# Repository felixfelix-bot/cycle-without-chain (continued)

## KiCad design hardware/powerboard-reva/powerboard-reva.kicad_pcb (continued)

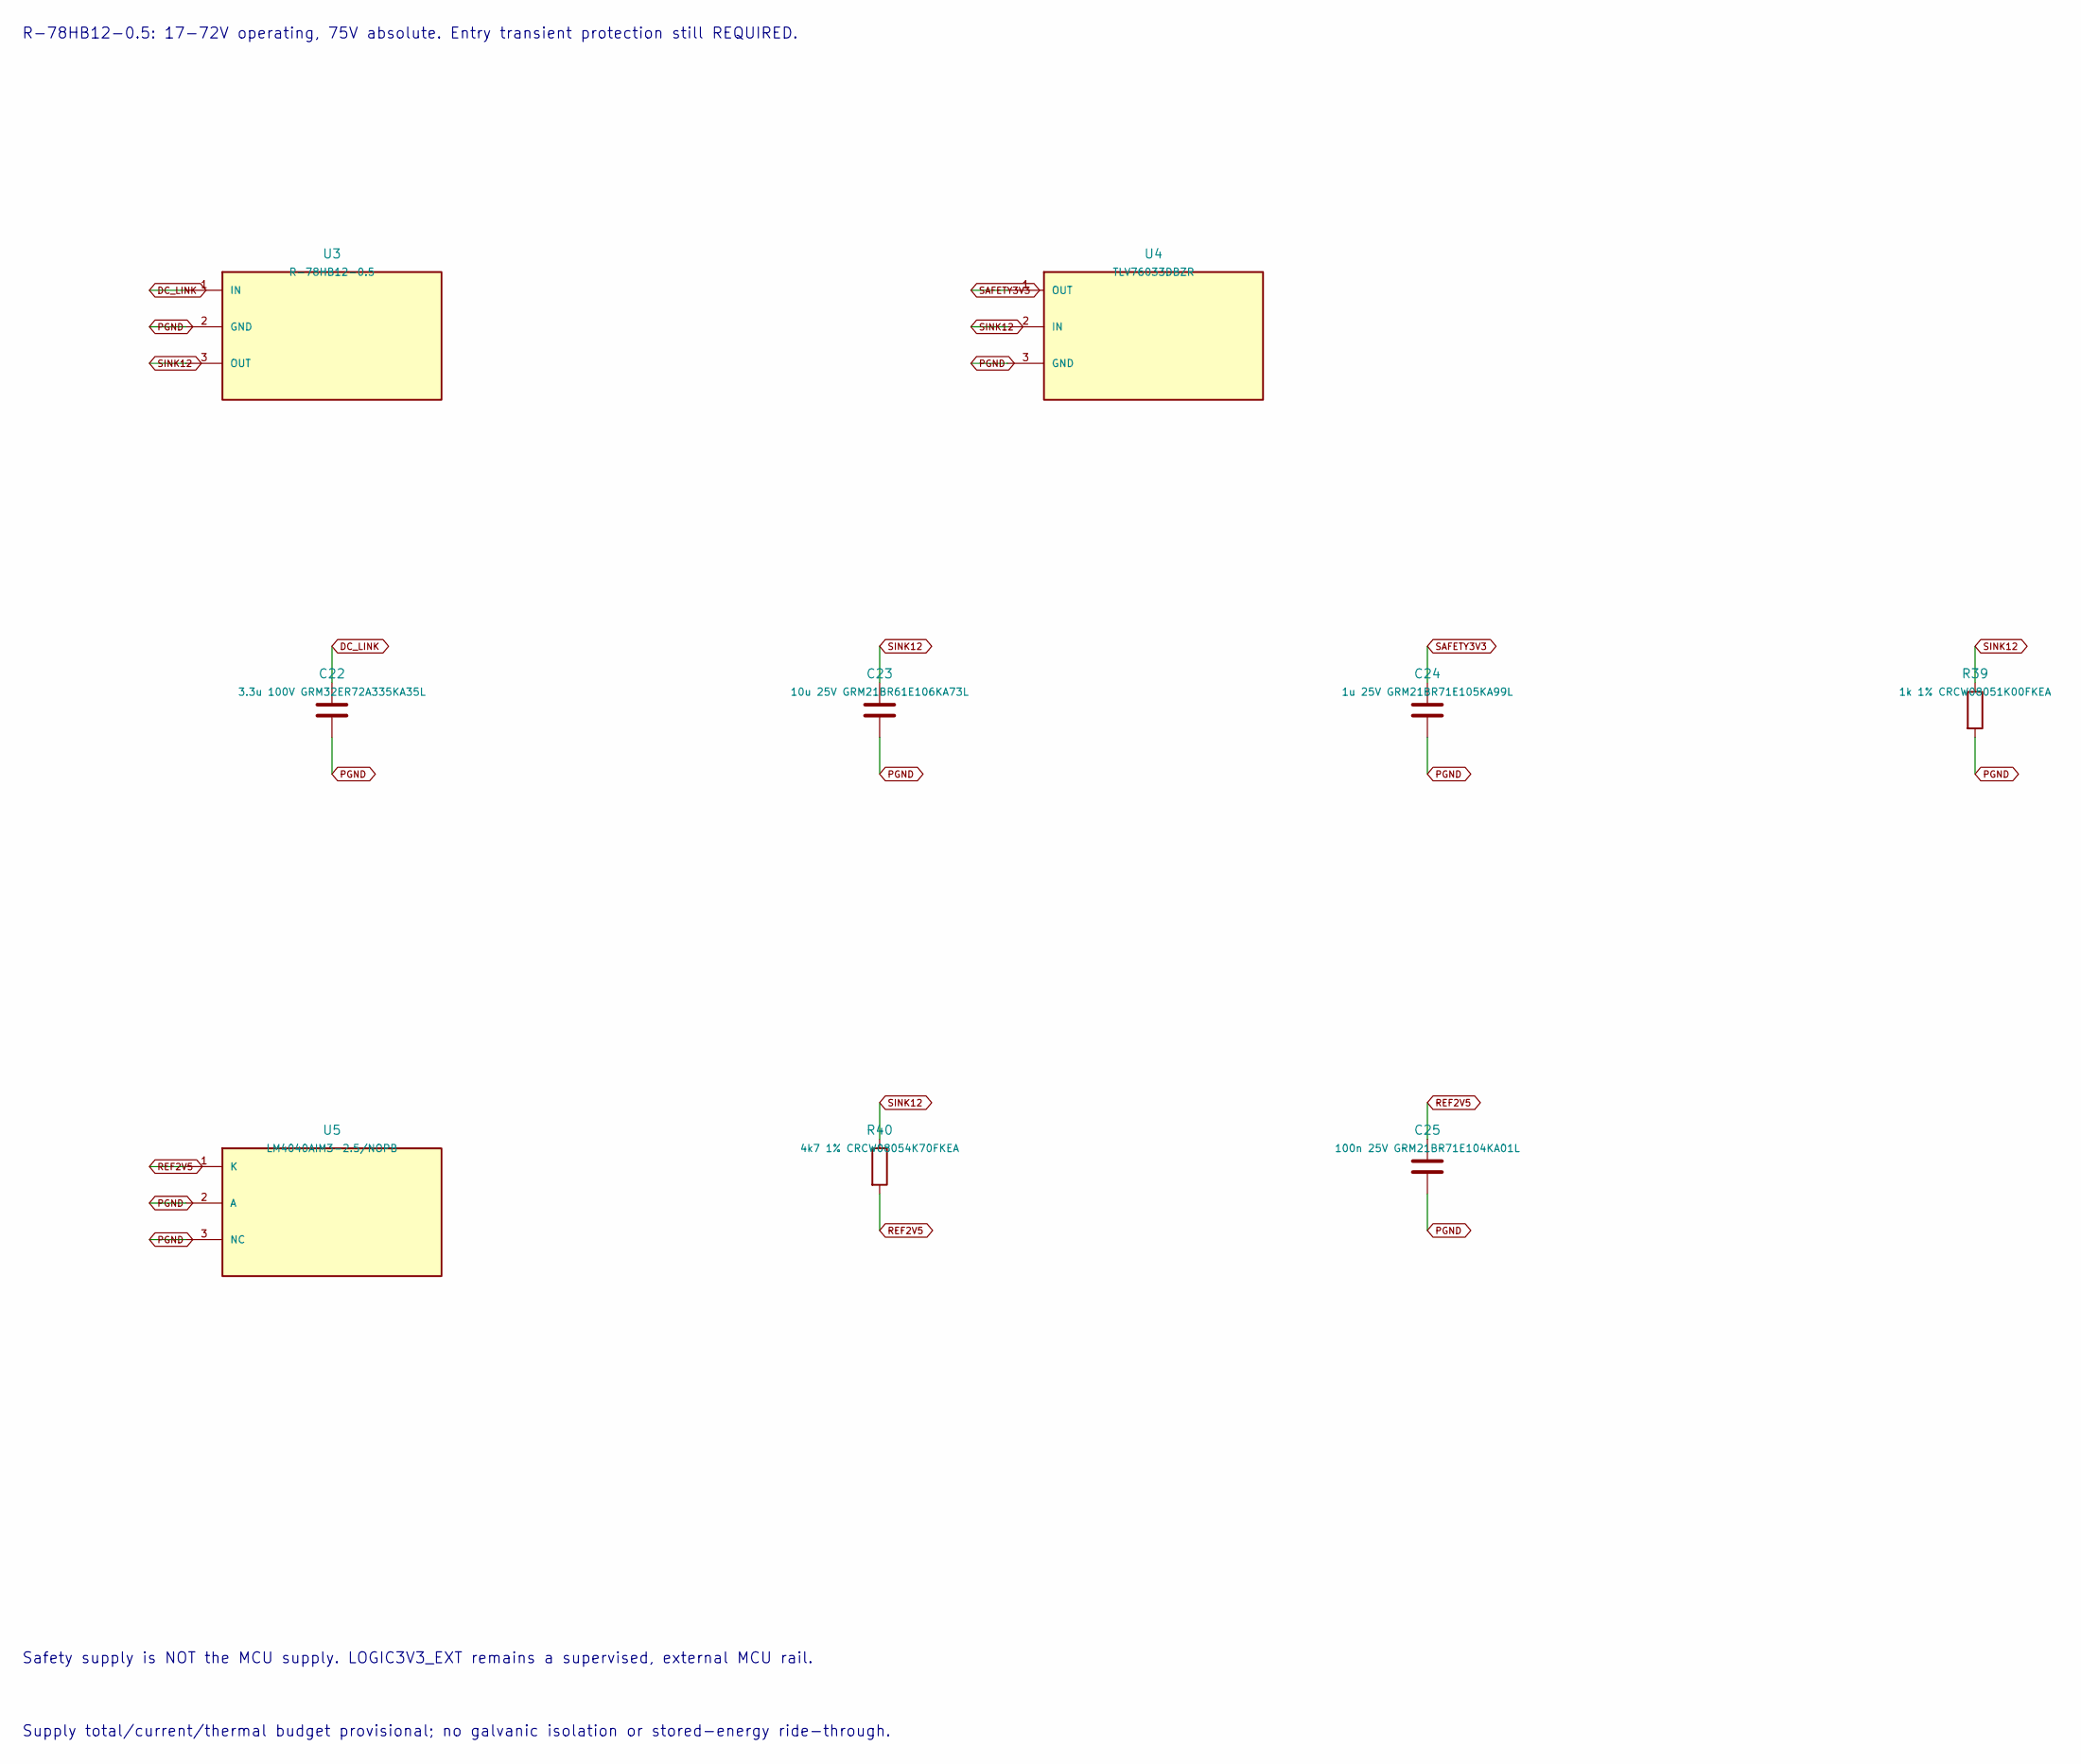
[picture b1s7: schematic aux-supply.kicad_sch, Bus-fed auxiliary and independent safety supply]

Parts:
C22: 3.3u 100V GRM32ER72A335KA35L; C_1210_3225Metric
C23: 10u 25V GRM21BR61E106KA73L; C_0805_2012Metric
C24: 1u 25V GRM21BR71E105KA99L; C_0805_2012Metric
C25: 100n 25V GRM21BR71E104KA01L; C_0805_2012Metric
R39: 1k 1% CRCW08051K00FKEA; R_0805_2012Metric
R40: 4k7 1% CRCW08054K70FKEA; R_0805_2012Metric
U3: R-78HB12-0.5; Converter_DCDC_RECOM_R-78HB-0.5_THT
U4: TLV76033DBZR; SOT-23
U5: LM4040AIM3-2.5/NOPB; SOT-23

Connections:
DC_LINK: C22.1, U3.1 (IN); also elsewhere on the board
PGND: C22.2, C23.2, C24.2, C25.2, R39.2, U3.2 (GND), U4.3 (GND), U5.2 (A), U5.3 (NC); also elsewhere on the board
REF2V5: C25.1, R40.2, U5.1 (K); also elsewhere on the board
SAFETY3V3: C24.1, U4.1 (OUT); also elsewhere on the board
SINK12: C23.1, R39.1, R40.1, U3.3 (OUT), U4.2 (IN); also elsewhere on the board

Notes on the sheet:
R-78HB12-0.5: 17-72V operating, 75V absolute. Entry transient protection still REQUIRED.
Safety supply is NOT the MCU supply. LOGIC3V3_EXT remains a supervised, external MCU rail.
Supply total/current/thermal budget provisional; no galvanic isolation or stored-energy ride-through.

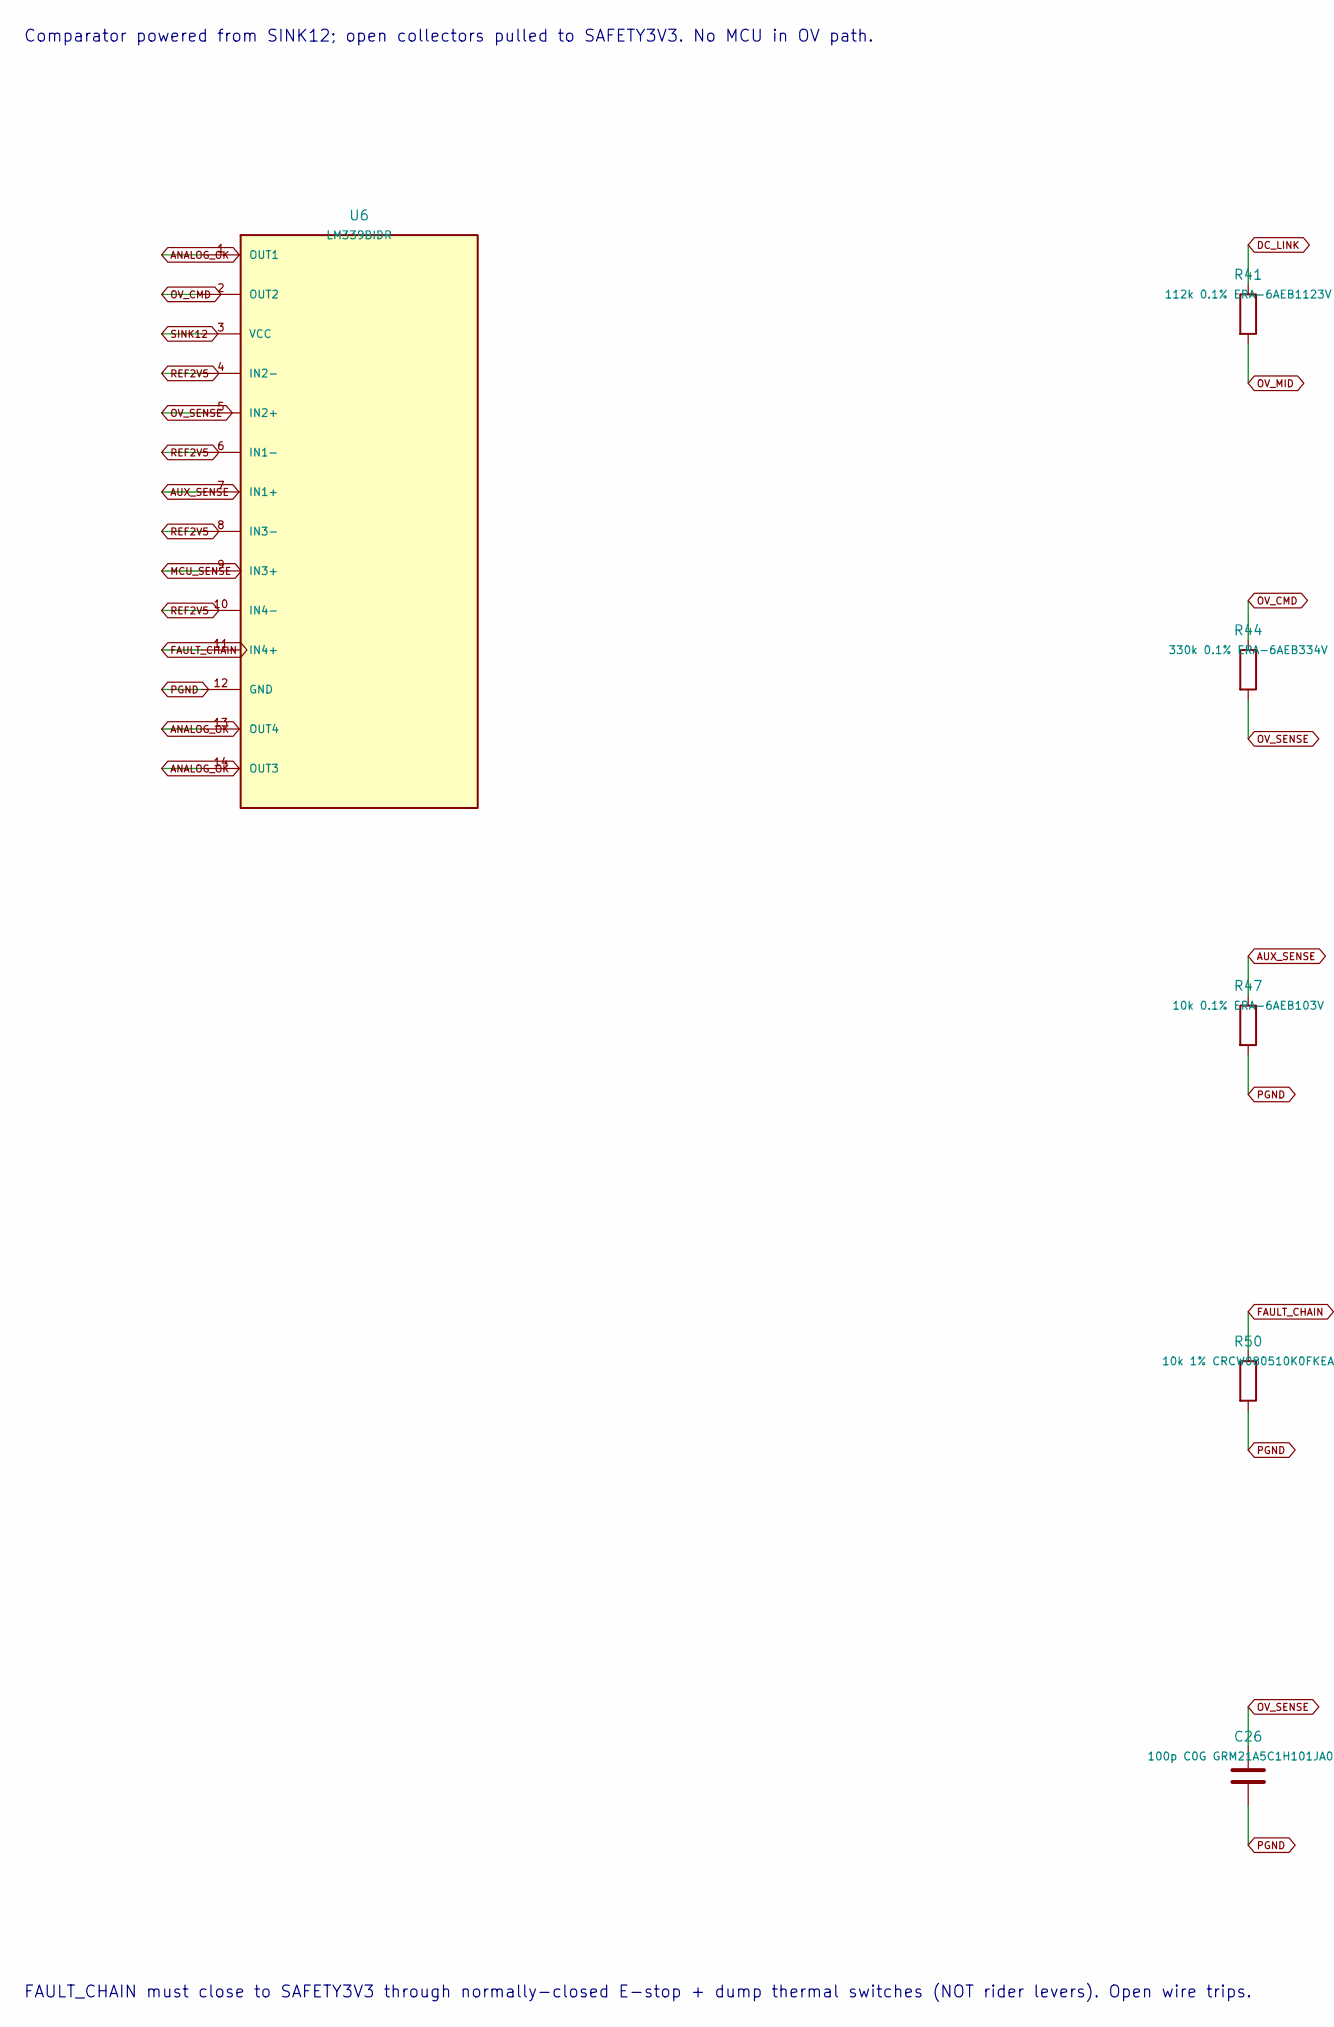
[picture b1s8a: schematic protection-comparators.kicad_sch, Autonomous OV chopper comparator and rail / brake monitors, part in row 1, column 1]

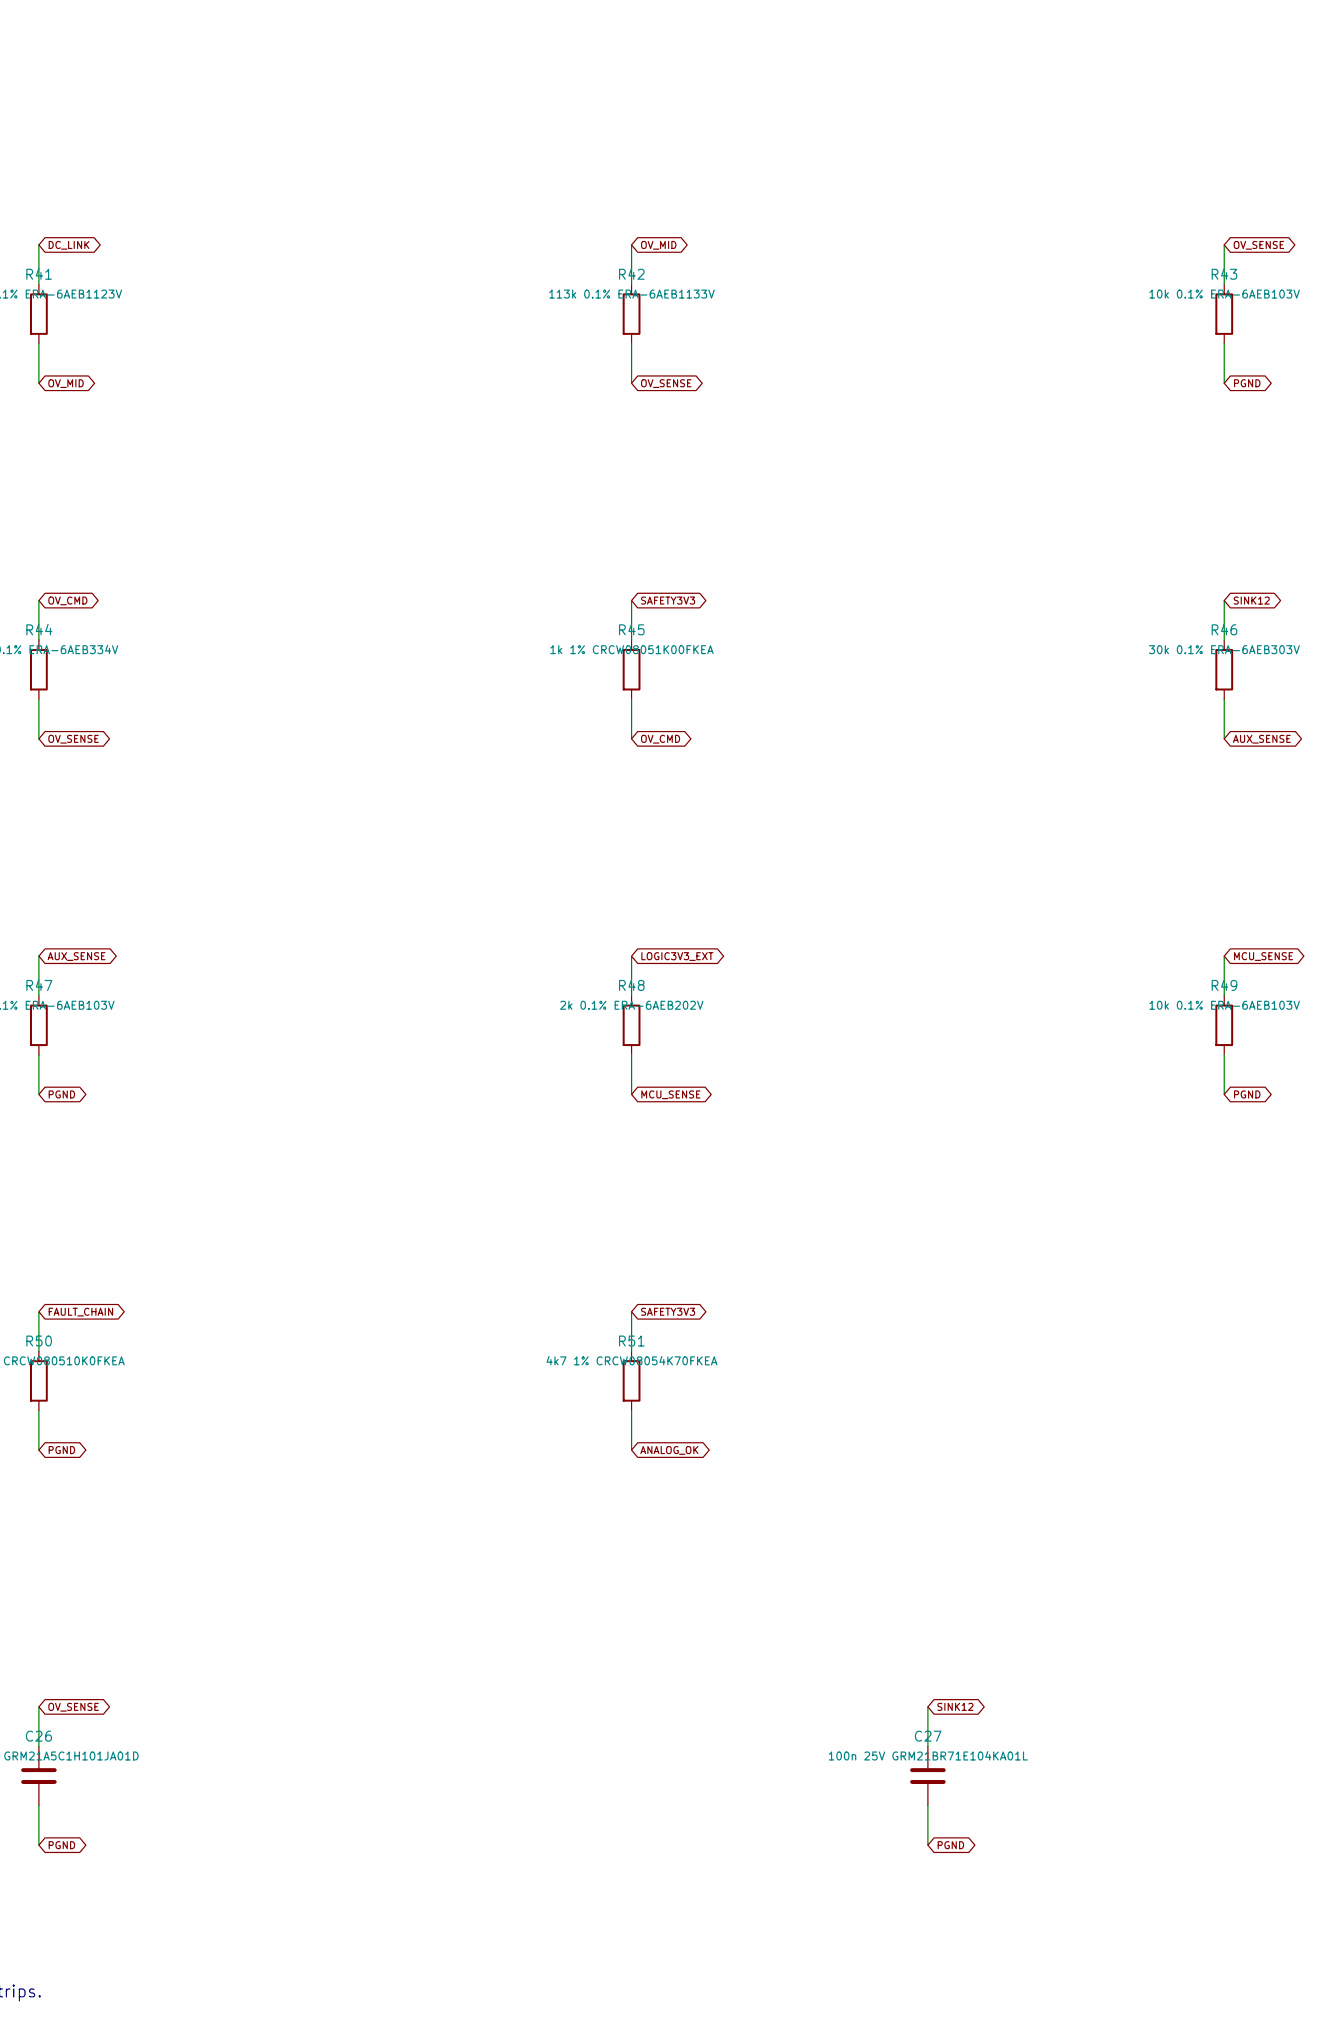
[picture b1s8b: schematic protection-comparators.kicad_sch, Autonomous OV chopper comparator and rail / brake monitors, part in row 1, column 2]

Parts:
C26: 100p C0G GRM21A5C1H101JA01D; C_0805_2012Metric
C27: 100n 25V GRM21BR71E104KA01L; C_0805_2012Metric
R41: 112k 0.1% ERA-6AEB1123V; R_0805_2012Metric
R42: 113k 0.1% ERA-6AEB1133V; R_0805_2012Metric
R43, R47, R49: 10k 0.1% ERA-6AEB103V; R_0805_2012Metric
R44: 330k 0.1% ERA-6AEB334V; R_0805_2012Metric
R45: 1k 1% CRCW08051K00FKEA; R_0805_2012Metric
R46: 30k 0.1% ERA-6AEB303V; R_0805_2012Metric
R48: 2k 0.1% ERA-6AEB202V; R_0805_2012Metric
R50: 10k 1% CRCW080510K0FKEA; R_0805_2012Metric
R51: 4k7 1% CRCW08054K70FKEA; R_0805_2012Metric
U6: LM339BIDR; SOIC-14_3.9x8.7mm_P1.27mm

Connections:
ANALOG_OK: R51.2, U6.1 (OUT1), U6.13 (OUT4), U6.14 (OUT3); also elsewhere on the board
AUX_SENSE: R46.2, R47.1, U6.7 (IN1+)
DC_LINK: R41.1; also elsewhere on the board
FAULT_CHAIN: R50.1, U6.11 (IN4+); also elsewhere on the board
LOGIC3V3_EXT: R48.1; also elsewhere on the board
MCU_SENSE: R48.2, R49.1, U6.9 (IN3+)
OV_CMD: R44.1, R45.2, U6.2 (OUT2); also elsewhere on the board
OV_MID: R41.2, R42.1
OV_SENSE: C26.1, R42.2, R43.1, R44.2, U6.5 (IN2+)
PGND: C26.2, C27.2, R43.2, R47.2, R49.2, R50.2, U6.12 (GND); also elsewhere on the board
REF2V5: U6.4 (IN2-), U6.6 (IN1-), U6.8 (IN3-), U6.10 (IN4-); also elsewhere on the board
SAFETY3V3: R45.1, R51.1; also elsewhere on the board
SINK12: C27.1, R46.1, U6.3 (VCC); also elsewhere on the board

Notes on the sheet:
Comparator powered from SINK12; open collectors pulled to SAFETY3V3. No MCU in OV path.
FAULT_CHAIN must close to SAFETY3V3 through normally-closed E-stop + dump thermal switches (NOT rider levers). Open wire trips.

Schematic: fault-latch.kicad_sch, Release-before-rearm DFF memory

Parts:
C28: 10n 5% C0G GRM21A5C1H103JA01D; C_0805_2012Metric
C29, C30, C31: 100n 25V GRM21BR71E104KA01L; C_0805_2012Metric
R52, R53, R55, R56, R57: 10k 1% CRCW080510K0FKEA; R_0805_2012Metric
R54, R60, R61: 1k 1% CRCW08051K00FKEA; R_0805_2012Metric
R58, R59: 100k CRCW0805100KFKEA; R_0805_2012Metric
U7, U8: SN74LVC1G74DCUR; VSSOP-8_2.3x2mm_P0.5mm
U9: TPS3823-33DBVR; SOT-23-5

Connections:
FAULT_LATCH: R59.1, U8.3 (Q_N)
GEN_ENABLE: R60.2; also elsewhere on the board
GEN_nFAULT: R56.2; also elsewhere on the board
HEALTHY: U7.6 (CLR_N), U8.6 (CLR_N); also elsewhere on the board
HUB_ENABLE: R61.2; also elsewhere on the board
HUB_nFAULT: R57.2; also elsewhere on the board
MCU_ARM: R53.1; also elsewhere on the board
PERMIT: U8.5 (Q); also elsewhere on the board
PGND: C28.2, C29.2, C30.2, C31.2, R52.2, R53.2, R54.2, R58.2, R59.2, U7.4 (GND), U8.4 (GND), U9.2 (GND); also elsewhere on the board
RELEASE_N: R58.1, U7.3 (Q_N)
RELEASE_SEEN: U7.5 (Q), U8.2 (D)
RESET_CLEAN: U8.1 (CLK); also elsewhere on the board
RESET_INV: U7.1 (CLK); also elsewhere on the board
RESET_RC: C28.1, R55.2; also elsewhere on the board
RESET_REQUEST: R52.1, R55.1; also elsewhere on the board
SAFETY3V3: C29.1, C30.1, C31.1, R56.1, R57.1, U7.2 (D), U7.7 (PRE_N), U7.8 (VCC), U8.7 (PRE_N), U8.8 (VCC), U9.3 (MR_N), U9.5 (VDD); also elsewhere on the board
TIMER_BREAK_OK: R60.1, R61.1; also elsewhere on the board
WDI: R54.1, U9.4 (WDI); also elsewhere on the board
WD_RESET_N: U9.1 (RESET_N); also elsewhere on the board

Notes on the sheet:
UNSAFE DRAFT: healthy release edge THEN press edge required. No automatic reset.
TPS3823 non-A: falling WDI only; hold low during RESET. Stuck RESET stays disabled.

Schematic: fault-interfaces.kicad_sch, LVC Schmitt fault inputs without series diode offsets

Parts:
C32, C33, C34, C35, C36, C37: 100n 25V GRM21BR71E104KA01L; C_0805_2012Metric
U11, U12: SN74LVC3G17DCUR; VSSOP-8_2.3x2mm_P0.5mm
U13, U14, U16: SN74LVC1G11DBVR; SOT-23-6
U15: SN74LVC1G04DBVR; SOT-23-5

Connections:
ANALOG_CLEAN: U11.7 (1Y), U13.1 (A)
ANALOG_OK: U11.1 (1A); also elsewhere on the board
ARM_CLEAN: U12.2 (3Y), U16.6 (C)
FAULTS_OK: U13.4 (Y), U14.1 (A)
GEN_OK: U11.5 (2Y), U13.3 (B)
GEN_nFAULT: U11.3 (2A); also elsewhere on the board
HEALTHY: U14.4 (Y), U16.1 (A); also elsewhere on the board
HUB_OK: U12.7 (1Y), U13.6 (C)
HUB_nFAULT: U12.1 (1A); also elsewhere on the board
MCU_ARM: U12.6 (3A); also elsewhere on the board
OC_OK: U14.6 (C); also elsewhere on the board
PERMIT: U16.3 (B); also elsewhere on the board
PGND: C32.2, C33.2, C34.2, C35.2, C36.2, C37.2, U11.4 (GND), U12.4 (GND), U13.2 (GND), U14.2 (GND), U15.1 (NC), U15.3 (GND), U16.2 (GND); also elsewhere on the board
RESET_CLEAN: U12.5 (2Y), U15.2 (A); also elsewhere on the board
RESET_INV: U15.4 (Y); also elsewhere on the board
RESET_RC: U12.3 (2A); also elsewhere on the board
SAFETY3V3: C32.1, C33.1, C34.1, C35.1, C36.1, C37.1, U11.8 (VCC), U12.8 (VCC), U13.5 (VCC), U14.5 (VCC), U15.5 (VCC), U16.5 (VCC); also elsewhere on the board
TIMER_BREAK_OK: U16.4 (Y); also elsewhere on the board
WD_OK: U11.2 (3Y), U14.3 (B)
WD_RESET_N: U11.6 (3A); also elsewhere on the board

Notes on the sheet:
Default OFF via async supervisor clear. Analog ramp/metastability NOT validated.

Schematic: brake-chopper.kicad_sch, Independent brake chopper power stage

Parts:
C38: 1u 25V GRM21BR71E105KA99L; C_0805_2012Metric
C39: 100n 25V GRM21BR71E104KA01L; C_0805_2012Metric
J6: EXTERNAL_DUMP_RESISTOR; R_Axial_DIN0207_L6.3mm_D2.5mm_P7.62mm_Horizontal
Q13: CSD19532Q5B; TDSON-8-1
R62: 10R CRCW080510R0FKEA; R_0805_2012Metric
R63: 2R2 CRCW08052R20FKEA; R_0805_2012Metric
R64: 10k CRCW080510K0FKEA; R_0805_2012Metric
U10: UCC27511DBVR; SOT-23-6

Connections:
CHOP_CMD: U10.6 (IN+); also elsewhere on the board
CHOP_GATE: Q13.4 (G), R62.2, R63.2, R64.1
CHOP_SINK: R63.1, U10.3 (OUTL)
CHOP_SOURCE: R62.1, U10.2 (OUTH)
DC_LINK: J6.1; also elsewhere on the board
DUMP_LOW: J6.2, Q13.5 (D)
PGND: C38.2, C39.2, Q13.1 (S), Q13.2 (S), Q13.3 (S), R64.2, U10.4 (GND), U10.5 (IN-); also elsewhere on the board
SINK12: C38.1, C39.1, U10.1 (VDD); also elsewhere on the board

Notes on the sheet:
Autonomous OV path ignores bridge ENABLE. External resistor is required across BRAKE_DUMP_RESISTOR connector pins.
Candidate: 2 x TE HSC3004R7J in series (9.4 ohm). Chassis/heatsink + NC thermal cutoff required.
No resistor cable clamp / fuse / SOA qualification yet. Loss of AUX supply loses bus sink: NOT FAIL SAFE.

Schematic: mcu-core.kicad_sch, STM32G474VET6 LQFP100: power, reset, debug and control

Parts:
C40: 100n NRST; C_0603_1608Metric
J7: SWD_3V3_TARGET_REFERENCE; PinHeader_1x06_P2.54mm_Vertical
J8: RESET_BUTTON_NORMALLY_OPEN; SW_SPST_TL3305A
R65: 10k NRST; R_0603_1608Metric
R66: 10k BOOT0; R_0603_1608Metric
U17: STM32G474VET6; LQFP-100_14x14mm_P0.5mm

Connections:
BRAKE_DUMP_PWM: U17.50 (PB11); also elsewhere on the board
DRV_MISO: U17.28 (PA6); also elsewhere on the board
DRV_MOSI: U17.92 (PB5); also elsewhere on the board
DRV_SCK: U17.27 (PA5); also elsewhere on the board
ENC_A: U17.93 (PB6); also elsewhere on the board
ENC_B: U17.94 (PB7); also elsewhere on the board
FAULT_CHAIN_SENSE: U17.61 (PD14); also elsewhere on the board
FSR_SAMPLE_ENABLE: U17.4 (PE5); also elsewhere on the board
GEN_HALL_1: U17.55 (PD8); also elsewhere on the board
GEN_HALL_2: U17.56 (PD9); also elsewhere on the board
GEN_HALL_3: U17.57 (PD10); also elsewhere on the board
GEN_INHA: U17.40 (PE9); also elsewhere on the board
GEN_INHB: U17.42 (PE11); also elsewhere on the board
GEN_INHC: U17.44 (PE13); also elsewhere on the board
GEN_INLA: U17.39 (PE8); also elsewhere on the board
GEN_INLB: U17.41 (PE10); also elsewhere on the board
GEN_INLC: U17.43 (PE12); also elsewhere on the board
GEN_SOA_ADC: U17.20 (PA0); also elsewhere on the board
GEN_SOB_ADC: U17.21 (PA1); also elsewhere on the board
GEN_SOC_ADC: U17.22 (PA2); also elsewhere on the board
GEN_nSCS: U17.62 (PD15); also elsewhere on the board
HUB_HALL_1: U17.58 (PD11); also elsewhere on the board
HUB_HALL_2: U17.59 (PD12); also elsewhere on the board
HUB_HALL_3: U17.60 (PD13); also elsewhere on the board
HUB_INHA: U17.65 (PC6); also elsewhere on the board
HUB_INHB: U17.66 (PC7); also elsewhere on the board
HUB_INHC: U17.67 (PC8); also elsewhere on the board
HUB_INLA: U17.29 (PA7); also elsewhere on the board
HUB_INLB: U17.32 (PB0); also elsewhere on the board
HUB_INLC: U17.33 (PB1); also elsewhere on the board
HUB_SOA_ADC: U17.15 (PC0); also elsewhere on the board
HUB_SOB_ADC: U17.16 (PC1); also elsewhere on the board
HUB_SOC_ADC: U17.17 (PC2); also elsewhere on the board
HUB_nSCS: U17.45 (PE14); also elsewhere on the board
LEFT_FSR_ADC: U17.18 (PC3); also elsewhere on the board
LEFT_SWITCH_ADC: U17.26 (PA4); also elsewhere on the board
LOGIC3V3_EXT: J7.1, R65.2, U17.6 (VBAT), U17.24 (VDD), U17.49 (VDD), U17.64 (VDD), U17.75 (VDD), U17.100 (VDD); also elsewhere on the board
MCU_ARM: U17.1 (PE2); also elsewhere on the board
MCU_BOOT0: R66.1, U17.95 (PB8)
MCU_NRST: C40.1, J7.4, J8.1, R65.1, U17.14 (PG10)
MCU_VDDA: U17.37 (VDDA); also elsewhere on the board
MCU_VREF: U17.36 (VREF+); also elsewhere on the board
PGND: C40.2, J7.5, J8.2, R66.2, U17.23 (VSS), U17.35 (VSSA), U17.48 (VSS), U17.63 (VSS), U17.74 (VSS), U17.99 (VSS); also elsewhere on the board
RESET_REQUEST: U17.3 (PE4); also elsewhere on the board
RIGHT_FSR_ADC: U17.25 (PA3); also elsewhere on the board
RIGHT_SWITCH_ADC: U17.34 (PB2); also elsewhere on the board
SWCLK: J7.3, U17.77 (PA14)
SWDIO: J7.2, U17.76 (PA13)
TIMER_BREAK_OK: U17.46 (PE15), U17.84 (PD2); also elsewhere on the board
WDI: U17.2 (PE3); also elsewhere on the board

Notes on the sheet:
HSI16 internal clock / PLL option: no HSE or LSE fitted; PF0/PF1 and PC14/15 explicit NC.
BOOT0 low; keep NRST function and configure boot option bytes before use. No firmware supplied.
BKIN active LOW required in TIM1/TIM8. Separate hardware ENABLE path remains intact.
NC GPIO: leave analog mode; HSI accuracy / PLL / ADC timing require validation.
MCU_ARM / RESET_REQUEST 10k and WDI 1k default-low resistors are on fault-latch page.

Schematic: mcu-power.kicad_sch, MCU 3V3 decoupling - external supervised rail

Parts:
C41: 100n 10V X7R pin24; C_0603_1608Metric
C42: 100n 10V X7R pin49; C_0603_1608Metric
C43: 100n 10V X7R pin64; C_0603_1608Metric
C44: 100n 10V X7R pin75; C_0603_1608Metric
C45: 100n 10V X7R pin100; C_0603_1608Metric
C46: 100n 10V X7R pin6; C_0603_1608Metric
C47: 4u7 10V X7R bulk; C_0603_1608Metric
C48, C50: 100n 10V X7R; C_0603_1608Metric
C49, C51: 1u 10V X7R; C_0603_1608Metric
R67, R68: 0R analog supply link; R_0603_1608Metric

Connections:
LOGIC3V3_EXT: C41.1, C42.1, C43.1, C44.1, C45.1, C46.1, C47.1, R67.1, R68.1; also elsewhere on the board
MCU_VDDA: C48.1, C49.1, R67.2; also elsewhere on the board
MCU_VREF: C50.1, C51.1, R68.2; also elsewhere on the board
PGND: C41.2, C42.2, C43.2, C44.2, C45.2, C46.2, C47.2, C48.2, C49.2, C50.2, C51.2; also elsewhere on the board

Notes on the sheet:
One 100n per VDD pin (24,49,64,75,100) plus VBAT pin6. Place each at pin / ground return.
VREFBUF MUST remain disabled: external 3V3 reference. VDDA/VREF tied via 0R; not precision isolated.
PWR_FLAG MCU_VDDA: arrives through R67 0R analog link, not a power-OUT

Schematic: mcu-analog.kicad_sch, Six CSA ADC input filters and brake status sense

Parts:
C52, C53, C54, C55, C56, C57: 1n C0G; C_0603_1608Metric
C58: 1n brake filter; C_0603_1608Metric
R69, R70, R71, R72, R73, R74: 100R 1%; R_0603_1608Metric
R75: 10k brake sense; R_0603_1608Metric
R76: 100k brake default; R_0603_1608Metric

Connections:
FAULT_CHAIN: R75.1; also elsewhere on the board
FAULT_CHAIN_SENSE: C58.1, R75.2, R76.1; also elsewhere on the board
GEN_SOA: R69.1; also elsewhere on the board
GEN_SOA_ADC: C52.1, R69.2; also elsewhere on the board
GEN_SOB: R70.1; also elsewhere on the board
GEN_SOB_ADC: C53.1, R70.2; also elsewhere on the board
GEN_SOC: R71.1; also elsewhere on the board
GEN_SOC_ADC: C54.1, R71.2; also elsewhere on the board
HUB_SOA: R72.1; also elsewhere on the board
HUB_SOA_ADC: C55.1, R72.2; also elsewhere on the board
HUB_SOB: R73.1; also elsewhere on the board
HUB_SOB_ADC: C56.1, R73.2; also elsewhere on the board
HUB_SOC: R74.1; also elsewhere on the board
HUB_SOC_ADC: C57.1, R74.2; also elsewhere on the board
PGND: C52.2, C53.2, C54.2, C55.2, C56.2, C57.2, C58.2, R76.2; also elsewhere on the board

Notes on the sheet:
100R / 1nF candidate filters: settling / sample aperture / CSA gain remain unqualified.
FAULT_CHAIN_SENSE is status ONLY. E-stop / thermal comparator and fault path do not depend on firmware.

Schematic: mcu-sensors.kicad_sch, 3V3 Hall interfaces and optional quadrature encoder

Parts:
C59, C60, C61, C62, C63, C64: 1n Hall filter; C_0603_1608Metric
C65, C66: 1n encoder filter; C_0603_1608Metric
J9: GEN_HALL_3V3_ONLY; PinHeader_1x05_P2.54mm_Vertical
J10: HUB_HALL_3V3_ONLY; PinHeader_1x05_P2.54mm_Vertical
J11: OPTIONAL_ENCODER_3V3_ONLY; PinHeader_1x05_P2.54mm_Vertical
R77, R79, R81, R83, R85, R87: 10k Hall pullup; R_0603_1608Metric
R78, R80, R82, R84, R86, R88: 1k Hall series; R_0603_1608Metric
R89, R91: 10k encoder pullup; R_0603_1608Metric
R90, R92: 1k encoder series; R_0603_1608Metric

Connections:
ENC_A: C65.1, R90.2; also elsewhere on the board
ENC_A_EXT: J11.3, R89.1, R90.1
ENC_B: C66.1, R92.2; also elsewhere on the board
ENC_B_EXT: J11.4, R91.1, R92.1
GEN_HALL_1: C59.1, R78.2; also elsewhere on the board
GEN_HALL_1_EXT: J9.3, R77.1, R78.1
GEN_HALL_2: C60.1, R80.2; also elsewhere on the board
GEN_HALL_2_EXT: J9.4, R79.1, R80.1
GEN_HALL_3: C61.1, R82.2; also elsewhere on the board
GEN_HALL_3_EXT: J9.5, R81.1, R82.1
HUB_HALL_1: C62.1, R84.2; also elsewhere on the board
HUB_HALL_1_EXT: J10.3, R83.1, R84.1
HUB_HALL_2: C63.1, R86.2; also elsewhere on the board
HUB_HALL_2_EXT: J10.4, R85.1, R86.1
HUB_HALL_3: C64.1, R88.2; also elsewhere on the board
HUB_HALL_3_EXT: J10.5, R87.1, R88.1
LOGIC3V3_EXT: J9.1, J10.1, J11.1, R77.2, R79.2, R81.2, R83.2, R85.2, R87.2, R89.2, R91.2; also elsewhere on the board
PGND: C59.2, C60.2, C61.2, C62.2, C63.2, C64.2, C65.2, C66.2, J9.2, J10.2, J11.2; also elsewhere on the board

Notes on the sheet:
3V3 ONLY: open-collector Hall / encoder or compatible 3V3 outputs. NO 5V tolerance claim.
Encoder PB6/PB7: TIM4_CH1/CH2 AF2 DS12288r5 T13 p74. Cable ESD/EMC protection unresolved.

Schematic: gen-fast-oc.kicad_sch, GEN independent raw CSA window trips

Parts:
C67, C68, C69: 100n X7R 25V; C_0805_2012Metric
Q14, Q15, Q16, Q17, Q18, Q19: 2N7002; SOT-23
R93, R96, R99: 100k 1% open SO bias; R_0805_2012Metric
R94, R95, R97, R98, R100, R101: 100k 1% gate default; R_0805_2012Metric
U18, U19, U20: TLV3202IDR; SOIC-8_3.9x4.9mm_P1.27mm

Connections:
GEN_SOA: R93.1, U18.2 (IN1-), U18.5 (IN2+); also elsewhere on the board
GEN_SOA_HI: Q15.1 (G), R95.1, U18.7 (OUT2)
GEN_SOA_LO: Q14.1 (G), R94.1, U18.1 (OUT1)
GEN_SOB: R96.1, U19.2 (IN1-), U19.5 (IN2+); also elsewhere on the board
GEN_SOB_HI: Q17.1 (G), R98.1, U19.7 (OUT2)
GEN_SOB_LO: Q16.1 (G), R97.1, U19.1 (OUT1)
GEN_SOC: R99.1, U20.2 (IN1-), U20.5 (IN2+); also elsewhere on the board
GEN_SOC_HI: Q19.1 (G), R101.1, U20.7 (OUT2)
GEN_SOC_LO: Q18.1 (G), R100.1, U20.1 (OUT1)
LOGIC3V3_EXT: C67.1, C68.1, C69.1, U18.8 (VCC), U19.8 (VCC), U20.8 (VCC); also elsewhere on the board
OC_HIGH_REF: U18.6 (IN2-), U19.6 (IN2-), U20.6 (IN2-); also elsewhere on the board
OC_LOW_REF: U18.3 (IN1+), U19.3 (IN1+), U20.3 (IN1+); also elsewhere on the board
OC_OK: Q14.3 (D), Q15.3 (D), Q16.3 (D), Q17.3 (D), Q18.3 (D), Q19.3 (D); also elsewhere on the board
PGND: C67.2, C68.2, C69.2, Q14.2 (S), Q15.2 (S), Q16.2 (S), Q17.2 (S), Q18.2 (S), Q19.2 (S), R93.2, R94.2, R95.2, R96.2, R97.2, R98.2, R99.2, R100.2, R101.2, U18.4 (GND), U19.4 (GND), U20.4 (GND); also elsewhere on the board

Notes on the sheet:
TLV3202IDR: positive SP-SN current DECREASES SO. Lower and upper limits both latch off.
No PWM blanking added. Low-side blind intervals remain; DRV VDS OCP contract mandatory.
Push-pull comparators drive separate sink FETs; outputs are NOT shorted together.
Open SO pulls down; stuck midpoint / shunt open / power-loss safety NOT proven. UNSAFE DRAFT.

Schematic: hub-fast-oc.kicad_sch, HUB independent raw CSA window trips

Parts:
C70, C71, C72: 100n X7R 25V; C_0805_2012Metric
Q20, Q21, Q22, Q23, Q24, Q25: 2N7002; SOT-23
R102, R105, R108: 100k 1% open SO bias; R_0805_2012Metric
R103, R104, R106, R107, R109, R110: 100k 1% gate default; R_0805_2012Metric
U21, U22, U23: TLV3202IDR; SOIC-8_3.9x4.9mm_P1.27mm

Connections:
HUB_SOA: R102.1, U21.2 (IN1-), U21.5 (IN2+); also elsewhere on the board
HUB_SOA_HI: Q21.1 (G), R104.1, U21.7 (OUT2)
HUB_SOA_LO: Q20.1 (G), R103.1, U21.1 (OUT1)
HUB_SOB: R105.1, U22.2 (IN1-), U22.5 (IN2+); also elsewhere on the board
HUB_SOB_HI: Q23.1 (G), R107.1, U22.7 (OUT2)
HUB_SOB_LO: Q22.1 (G), R106.1, U22.1 (OUT1)
HUB_SOC: R108.1, U23.2 (IN1-), U23.5 (IN2+); also elsewhere on the board
HUB_SOC_HI: Q25.1 (G), R110.1, U23.7 (OUT2)
HUB_SOC_LO: Q24.1 (G), R109.1, U23.1 (OUT1)
LOGIC3V3_EXT: C70.1, C71.1, C72.1, U21.8 (VCC), U22.8 (VCC), U23.8 (VCC); also elsewhere on the board
OC_HIGH_REF: U21.6 (IN2-), U22.6 (IN2-), U23.6 (IN2-); also elsewhere on the board
OC_LOW_REF: U21.3 (IN1+), U22.3 (IN1+), U23.3 (IN1+); also elsewhere on the board
OC_OK: Q20.3 (D), Q21.3 (D), Q22.3 (D), Q23.3 (D), Q24.3 (D), Q25.3 (D); also elsewhere on the board
PGND: C70.2, C71.2, C72.2, Q20.2 (S), Q21.2 (S), Q22.2 (S), Q23.2 (S), Q24.2 (S), Q25.2 (S), R102.2, R103.2, R104.2, R105.2, R106.2, R107.2, R108.2, R109.2, R110.2, U21.4 (GND), U22.4 (GND), U23.4 (GND); also elsewhere on the board

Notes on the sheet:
TLV3202IDR: positive SP-SN current DECREASES SO. Lower and upper limits both latch off.
No PWM blanking added. Low-side blind intervals remain; DRV VDS OCP contract mandatory.
Push-pull comparators drive separate sink FETs; outputs are NOT shorted together.
Open SO pulls down; stuck midpoint / shunt open / power-loss safety NOT proven. UNSAFE DRAFT.

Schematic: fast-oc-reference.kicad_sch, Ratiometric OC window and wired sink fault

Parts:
R111, R114: 28k7 0.1%; R_0805_2012Metric
R112, R113: 10k 0.1%; R_0805_2012Metric
R115: 4k7 1%; R_0805_2012Metric

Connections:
LOGIC3V3_EXT: R111.1, R113.1; also elsewhere on the board
OC_HIGH_REF: R113.2, R114.1; also elsewhere on the board
OC_LOW_REF: R111.2, R112.1; also elsewhere on the board
OC_OK: R115.2; also elsewhere on the board
PGND: R112.2, R114.2; also elsewhere on the board
SAFETY3V3: R115.1; also elsewhere on the board

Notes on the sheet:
VREF tracks actual driver LOGIC3V3_EXT: 0.852713 / 2.447287 V nominal at 3.3 V.
OC_OK directly enters U14.6, clears U7/U8 and U16: both ENABLE and TIM1/TIM8 break.
No external hysteresis or blanking: first crossing latches. Noise/settling and sink delay unqualified.
Nominal trip +/-19.932 A; provisional measurement +/-30 A. Commissioning cap 10 A, NOT release.

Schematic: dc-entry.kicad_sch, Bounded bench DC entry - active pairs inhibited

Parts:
C73, C74: 470u 100V UHE2A471MHD +/-20%; CP_Radial_D16.0mm_P7.50mm
D20: STPS30100ST reverse clamp ONLY not reverse blocker; TO-277A
F1: KLKD020CN 20A 600VDC; Fuseholder_Littelfuse_100_series_5x20mm
J40: Anderson 992G1 SB50 keyed SOURCE; AMASS_XT60-F_1x02_P7.20mm_Vertical
J43: Kelvin BUS measurement isolated instrument ONLY; PinHeader_1x04_P2.54mm_Vertical
R116: 22R 1% RH05022R00FE02 pulse UNQUALIFIED; R_Axial_DIN0207_L6.3mm_D2.5mm_P7.62mm_Horizontal
R117: 2m 1% WSLP2512R0020FEA Kelvin; R_2512_6332Metric
R118: 10k 1% RH02510K00FE02 always-on bleed; R_0805_2012Metric

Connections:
BUS_SHUNT_HI: J43.1, R116.2, R117.1; also elsewhere on the board
DC_LINK: C73.1, C74.1, D20.1 (K), J43.2, J43.3, R117.2, R118.1; also elsewhere on the board
ENTRY_FUSED: F1.2; also elsewhere on the board
PGND: C73.2, C74.2, D20.2 (A), J40.2, J43.4, R118.2; also elsewhere on the board
PRECHARGE_R: R116.1; also elsewhere on the board
SOURCE_POS: F1.1, J40.1

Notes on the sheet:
NOT SAFE TO ENERGIZE integrated drive. No automatic sequencing or reverse-blocking guarantee.
36-58.4V bench interface, 15A TARGET ONLY. Disconnect PM machines before source removal.
J41/J42 removed. MAIN/PRE physical pairs are inhibited on separate sheets. NO ENERGIZE.
J43 raw high common mode: NOT MCU ADC. D20/fuse reverse-fault coordination UNQUALIFIED.
Sink/chopper stays DC_LINK side. MAIN open does NOT make bus safe: PM backfeeds via diodes.
PWR_FLAG DC_LINK: external pack via J43 / R116 / inhibit FETs; no power-OUT symbol
PWR_FLAG PGND: single-point return; ground is a plane, not a power-OUT pin

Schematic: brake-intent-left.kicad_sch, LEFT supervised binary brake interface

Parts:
C75: 10n ADC filter; C_0805_2012Metric
D32: PESD3V3U1UL; D_SOD-882
D36: BAT54S; SOT-23
J44: LEFT_BINARY_SWITCH_ONLY; SW_SPST_TL3305A
R119: 10k 1% signal current limit; R_0805_2012Metric
R120: 10k 1% switch bias; R_0805_2012Metric

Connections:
LEFT_SWITCH_ADC: C75.1, D36.3 (COM), R119.2; also elsewhere on the board
LEFT_SWITCH_EXT: D32.1 (A1), J44.2, R119.1, R120.1; also elsewhere on the board
LOGIC3V3_EXT: D36.2 (K), R120.2; also elsewhere on the board
PGND: C75.2, D32.2 (A2), D36.1 (A), J44.1; also elsewhere on the board

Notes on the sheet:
Candidate only: reversible non-load-bearing lever sensors. NO mechanical brake cable alteration.
External switch harness: 4k7 series + (10k parallel NC switch). Release=1.055V; press=1.964V.
Open=3V3 / short=0V faults via ADC; firmware NOT implemented. Clamp injection/power-off NOT qualified.

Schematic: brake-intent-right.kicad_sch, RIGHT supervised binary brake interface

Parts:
C76: 10n ADC filter; C_0805_2012Metric
D33: PESD3V3U1UL; D_SOD-882
D37: BAT54S; SOT-23
J45: RIGHT_BINARY_SWITCH_ONLY; SW_SPST_TL3305A
R121: 10k 1% signal current limit; R_0805_2012Metric
R122: 10k 1% switch bias; R_0805_2012Metric

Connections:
LOGIC3V3_EXT: D37.2 (K), R122.2; also elsewhere on the board
PGND: C76.2, D33.2 (A2), D37.1 (A), J45.1; also elsewhere on the board
RIGHT_SWITCH_ADC: C76.1, D37.3 (COM), R121.2; also elsewhere on the board
RIGHT_SWITCH_EXT: D33.1 (A1), J45.2, R121.1, R122.1; also elsewhere on the board

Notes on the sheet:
Candidate only: reversible non-load-bearing lever sensors. NO mechanical brake cable alteration.
External switch harness: 4k7 series + (10k parallel NC switch). Release=1.055V; press=1.964V.
Open=3V3 / short=0V faults via ADC; firmware NOT implemented. Clamp injection/power-off NOT qualified.

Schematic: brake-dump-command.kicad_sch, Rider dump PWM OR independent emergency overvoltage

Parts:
C77: 100n AND decoupling; C_0805_2012Metric
C78: 100n OR decoupling; C_0805_2012Metric
R123: 10k dump PWM default off; R_0805_2012Metric
U24: SN74LVC1G32DBVR; SOT-23-5
U25: SN74LVC1G08DBVR; SOT-23-5

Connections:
BRAKE_DUMP_PERMITTED: U24.2, U25.4
BRAKE_DUMP_PWM: R123.1, U25.1; also elsewhere on the board
CHOP_CMD: U24.4; also elsewhere on the board
OV_CMD: U24.1; also elsewhere on the board
PGND: C77.2, C78.2, R123.2, U24.3 (GND), U25.3 (GND); also elsewhere on the board
SAFETY3V3: C77.1, C78.1, U24.5 (VCC), U25.5 (VCC); also elsewhere on the board
TIMER_BREAK_OK: U25.2; also elsewhere on the board

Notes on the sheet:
OV always overrides MCU PWM. Normal PWM must require valid rider request AND cool dump permission.
PWM AND TIMER_BREAK_OK: watchdog / E-stop / thermal fault kill normal dump. OV bypass retained.
No torque-sign hardware guard. Firmware must disarm on sensor fault; watchdog / OC / E-stop remain hardware kills.
Firmware entirely unimplemented. Do not energize; brake command control only a design contract.
